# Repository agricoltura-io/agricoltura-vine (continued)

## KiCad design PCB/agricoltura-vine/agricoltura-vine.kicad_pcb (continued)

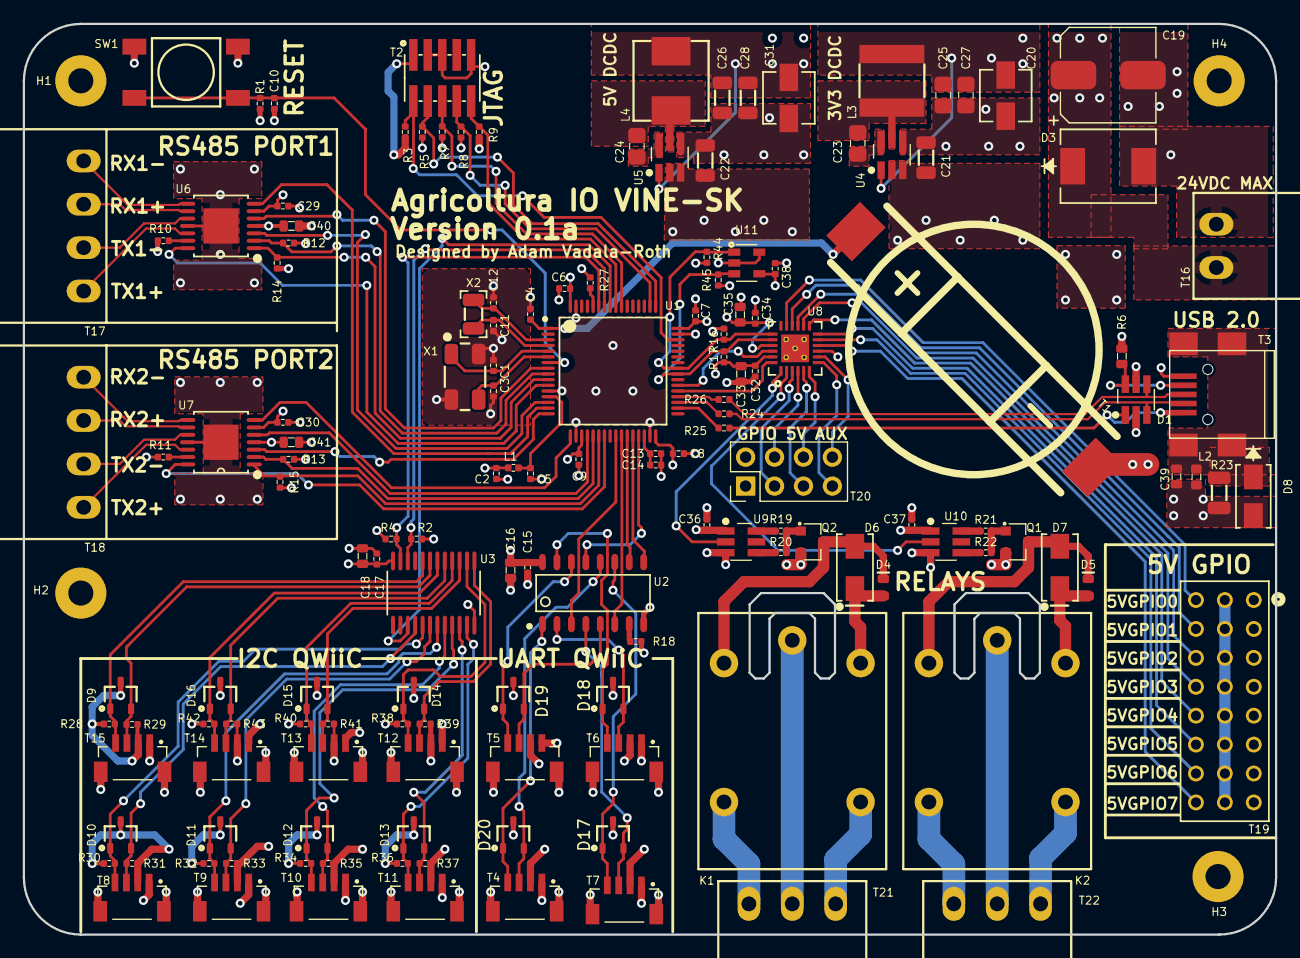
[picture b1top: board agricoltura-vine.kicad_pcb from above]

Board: 4 copper layers, 110.0 x 80.0 mm, 153 parts (0 on the bottom side), 120 nets.

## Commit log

2020-06-17 Datasheets and Schematic
    started laying out the schematic, STM32 part copied from SunLeaf V2. Datasheets for components in use added to repo.
2020-06-17 Schematic process
    scheamtics laid out for all board subsyhstems, connecting MCU to subsystems still in progress, power yet to be designed.
2020-06-18 Power Supplies
    designed power supplies for 3.3v and 5V as well as 24VAC input
2020-06-18 5V Logic, Connector swap, and I2C refactor
    Added 5V IO logic, changed connectors over to grove style SMT, I2C refactored to use 8x mux instead fo two 4x mux.
2020-06-18 Power supplies
    Both power supplies redsigned around new ICs for 2A of each voltage, since we have no idea how much current peripherals will be using.
2020-06-18 Schematic Pass 1
    All subsystem schematics are completed in their first pass, some features scaled back to make design more practical.
2020-06-18 Schematic and Readme
    Readme updated with latest feature set, and schematic pages interconnected.
2020-06-18 Board
    Board shape defined, though subject to change. Schematic anotated and parts exported to board.
2020-06-19 Board Size , Connectors and Layout
    Changed board size and shape, started layout, swapped connectors over.
2020-06-20 Board shape and Rough PLacement
    Board shape adjusted to have smaller rounded corners increasing usable space of board shape. Finished rough placement of all the components, no routing yet. Debating connector style and form factor. 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
2020-06-21 Route Started Connectors Changed
    Changed to QWIIC style connectors and adjusted pinning of RJ45s, but switching to screw terminal header in next commit. THis is a backup
2020-06-22 Routing and New RS485
    swapped over the RS485 chip to a new one and started routing the board.
2020-06-23 Routing progress
    RS845 ports routed, UART mux routed, sensor ports reoriented. Starting to come together.
2020-06-23 Majopr Progress
    Board shape enlarged to simplify layout and accomodate larger size parts for sisterboard like Ivy. QWIIC connectors flipped to be correct, signals were oriented incorrectly in past revisions.
2020-06-24 IO Expander
    added IO expander for 5V IOs
2020-06-27 Big Update
    Dropped 8 5V outputs in favor of two relays. Ditched microchip IO expander for a Ti one that does level conversion for outputs, eliminates Ti bidriectional converter and 74 line driver from design, s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
2020-06-29 Relay Driver Circuit, Board Size Change
    Added the Relay driver circuitry, increased size of board tobetter acccomodate relays, figuredout the powerplane topology to get 5Vs where it needs to go.
2020-06-30 First pass of board
    Finished routing first pass of PCB
2020-06-30 Adjustments
    Moved Relays closer to edge, pushed VBAT battery holder back towards USB, optimized USB TVS circuit. Broke out extra 5V GPIOs to header
2020-07-02 Netlabels and Datasheets
    Removed datasheets for parts no longer in design, added datasheet for RS485 transceiver. Added netlabels for RS485 signals.
2020-07-03 Connector Swap
    Switched over to dedicated connectors per relay
2020-07-17 ST Datasheets
    ST datasheets added
2020-07-20 EEPROM
    Added EEPROM chip to design, also beefed up USB grounding and shock protection
2020-07-21 Added EEProm
    Eeprom added and routed in circuit board, USB resitors added. TVS diodes and pullups added to I2C ports not yet placed.
2020-07-29 Board tweaks
    TVS diodes added, board needs routing, a lot of board has been tweaked, more to come.
2020-08-09 TVS Diodes
    TVS diodes and pullups added to sensor connectors, implemented in schematic and board.
2020-08-18 DC Power
    Power input section converted to 24VDC Max input instead of AC. A proper AC to DC power supply would need more components to be properly implmented and not require redesign of the DCDC regulators. Al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
2024-03-26 Added license
    added license and updated kicad project
